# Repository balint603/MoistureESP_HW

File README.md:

# Hardware for MoistureESP project.
## Description
This project aims to use the ESP32 in low power modes, discover its capabilites for low power application. Also, this sensor project would be useful for home gardens not to forget watering.
This is not a complete product, it can be considered as a devboard.

*Software component not published yet.*
*3D case not published yet.*
## Software
See repository: [https://github.com/balint603/moist](https://github.com/balint603/moist)
## Components
- *This PCB project*
- ESP32-WROOM-32
- SOILCAP-V20 humidity measure
- DS18B20 sensor
- *SW not ready yet*
- *BMS configuration not ready yet*
## Features
- BMS cell protection.
- Overvoltage protection for battery input.
- Charger with USB (not tested).
- Wi-Fi MQTT data transmission.
- Selectable sensor measure interval.
## Interfaces
- Wi-Fi communication aimed to be used for sharing sensor data.
- Analog input for moisture sensor board (SOILCAP-V20).
- 1-Wire interface for DS18B20 temperature sensor.
- BMS I2C lines.
- UART for ESP programming and debug with RTS, DTS secondary programming feature.
- *Optional I2C for display.*
## Power
- Sized for 18650 battery cell, BMS tested with NCR18650B.
- Optinally Li-ion charger can be connected.
- Built-in USB charger was not tested.
### BMS configuration
1. Disable 2 cell: Settings->DA configuration->CC0 bit needs to be set to zero.
    - Otherwise it causes CUV and discharge FET will not turn on.
## Prerequisites
- KiCAD v10.0.0 

## Release
- V1.0: USB charger not tested.

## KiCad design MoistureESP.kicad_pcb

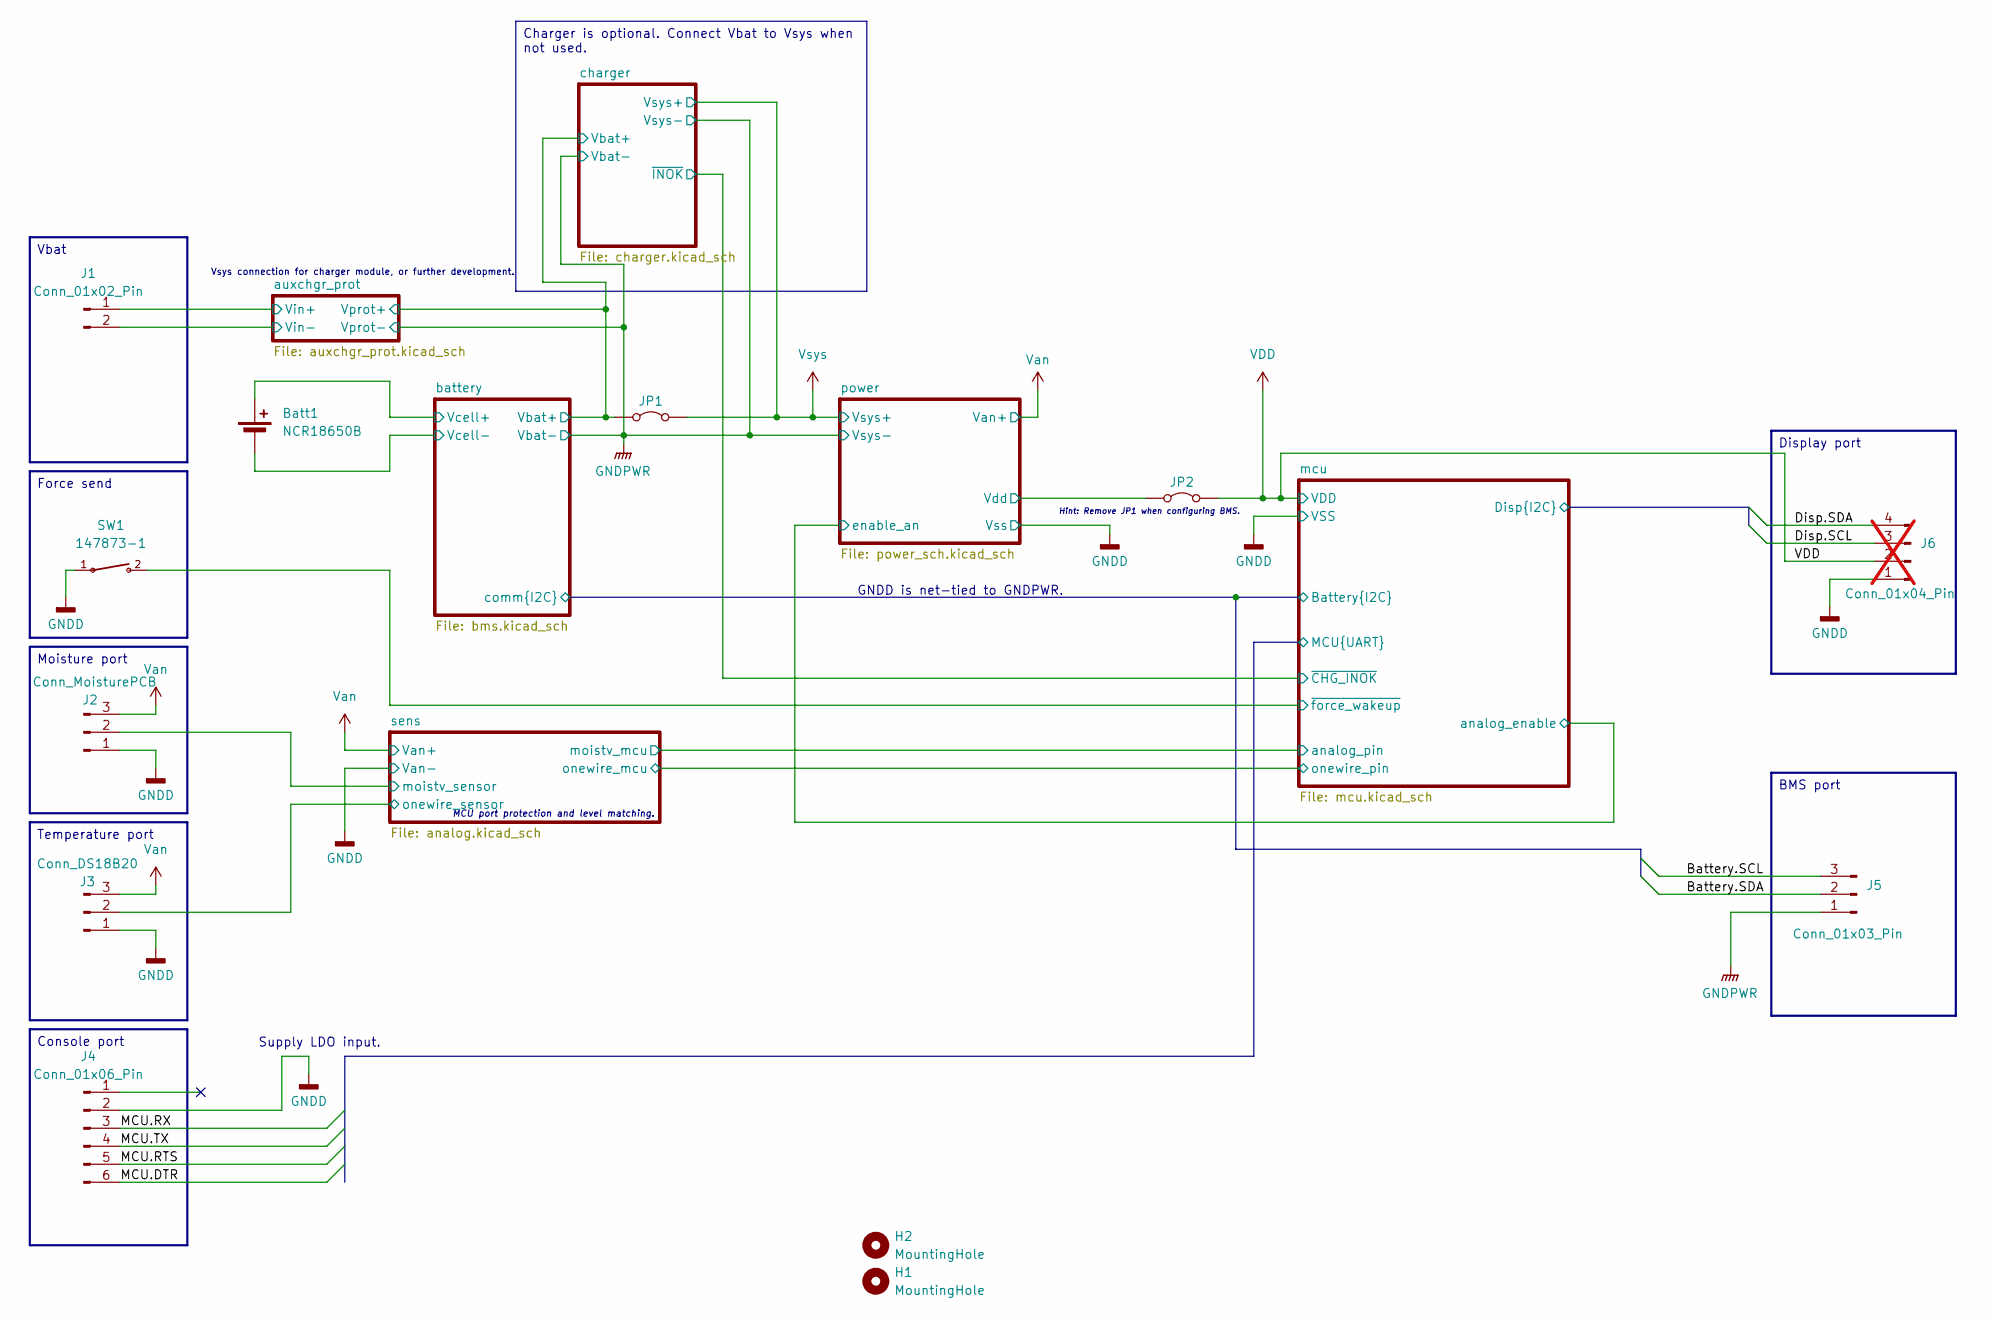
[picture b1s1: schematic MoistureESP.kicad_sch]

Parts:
Batt1: NCR18650B; NCR18650
H1, H2: MountingHole; MountingHole_2.7mm_M2.5_DIN965
J1: Conn_01x02_Pin; PinHeader_1x02_P2.54mm_Vertical
J2: Conn_MoisturePCB; sensorwirepads3x1
J3: Conn_DS18B20; sensorwirepads3x1
J4: Conn_01x06_Pin; PinHeader_1x06_P2.54mm_Vertical
J5: Conn_01x03_Pin; PinHeader_1x03_P2.54mm_Vertical
J6: Conn_01x04_Pin; PinHeader_1x04_P2.54mm_Vertical; not fitted
JP1, JP2: Jumper_2_Bridged; PinHeader_1x02_P2.54mm_Vertical
SW1: 147873-1; SW_147873-1; PARTREV K3

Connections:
/auxchgr_prot/Vin+: J1.1; also elsewhere on the board
/battery/Vcell+: Batt1.1 (+); also elsewhere on the board
/battery/comm.SCL: J5.3; also elsewhere on the board
/battery/comm.SDA: J5.2; also elsewhere on the board
/charger/VBat: JP1.1 (A); also elsewhere on the board
/mcu/Disp.SCL: J6.3; also elsewhere on the board
/mcu/Disp.SDA: J6.4; also elsewhere on the board
/mcu/MCU.DTR: J4.6; also elsewhere on the board
/mcu/MCU.RTS: J4.5; also elsewhere on the board
/mcu/MCU.RX: J4.3; also elsewhere on the board
/mcu/MCU.TX: J4.4; also elsewhere on the board
/mcu/onewire_pin: J3.2; also elsewhere on the board
/mcu/~force_wakeup: SW1.2; also elsewhere on the board
/power/Vdd: JP2.1 (A); also elsewhere on the board
/sens/moistv_sensor: J2.2; also elsewhere on the board
CGND: Batt1.2 (-); also elsewhere on the board
GNDD: J2.1, J3.1, J4.2, J6.1, SW1.1; also elsewhere on the board
GNDPWR: J1.2, J5.1; also elsewhere on the board
VDD: J6.2, JP2.2 (B); also elsewhere on the board
Van: J2.3, J3.3; also elsewhere on the board
Vsys: JP1.2 (B); also elsewhere on the board

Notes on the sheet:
Vsys connection for charger module, or further development.
MCU port protection and level matching.
Supply LDO input.
GNDD is net-tied to GNDPWR.
Hint: Remove JP1 when configuring BMS.
Vbat
Temperature port
Force send
Console port
Charger is optional. Connect Vbat to Vsys when not used.
Display port
BMS port
Moisture port

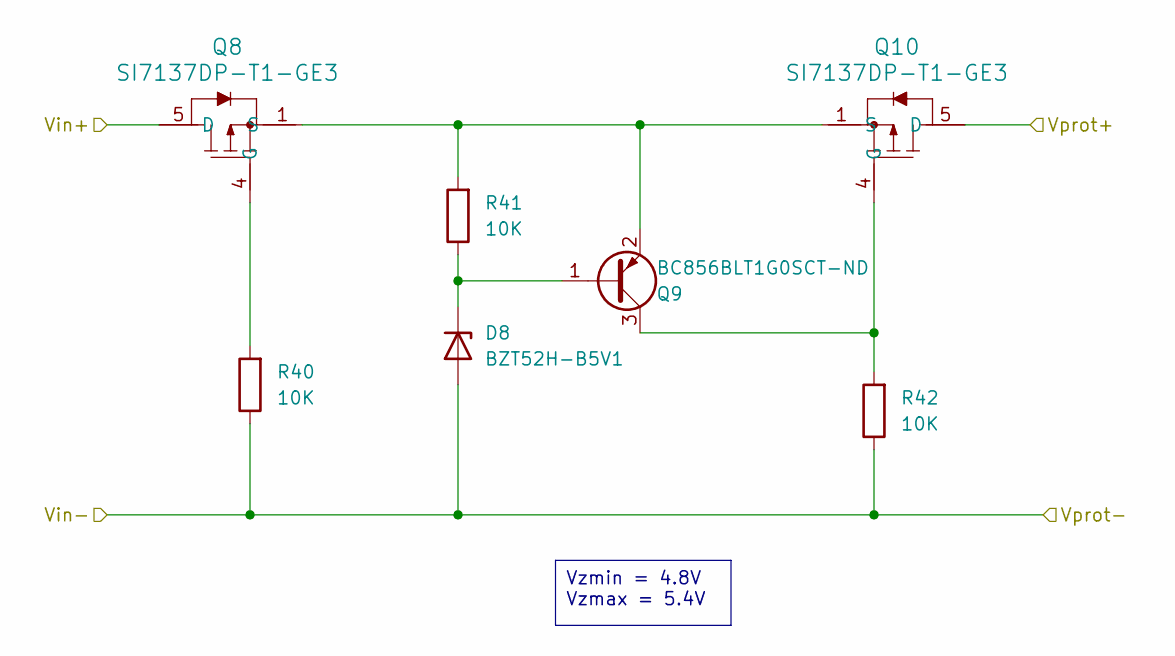
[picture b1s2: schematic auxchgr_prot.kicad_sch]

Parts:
D8: BZT52H-B5V1; D_SOD-123F
Q8, Q10: SI7137DP-T1-GE3; MOSFET_7DP-T1-GE3_VIS
Q9: BC856BLT1G0SCT-ND; SOT-23
R40, R41, R42: 10K; R_0603_1608Metric_Pad0.98x0.95mm_HandSolder

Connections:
/auxchgr_prot/Vin+: Q8.5 (D); also elsewhere on the board
/charger/VBat: Q10.5 (D); also elsewhere on the board
GNDPWR: D8.2 (A), R40.1, R42.1; also elsewhere on the board
unnamed: D8.1 (K), Q9.1 (B), R41.1
unnamed: Q8.4 (G), R40.2
unnamed: Q8.1 (S), Q8.2 (S), Q8.3 (S), Q9.2 (E), Q10.1 (S), Q10.2 (S), Q10.3 (S), R41.2
unnamed: Q9.3 (C), Q10.4 (G), R42.2

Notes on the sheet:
Vzmin = 4.8V Vzmax = 5.4V

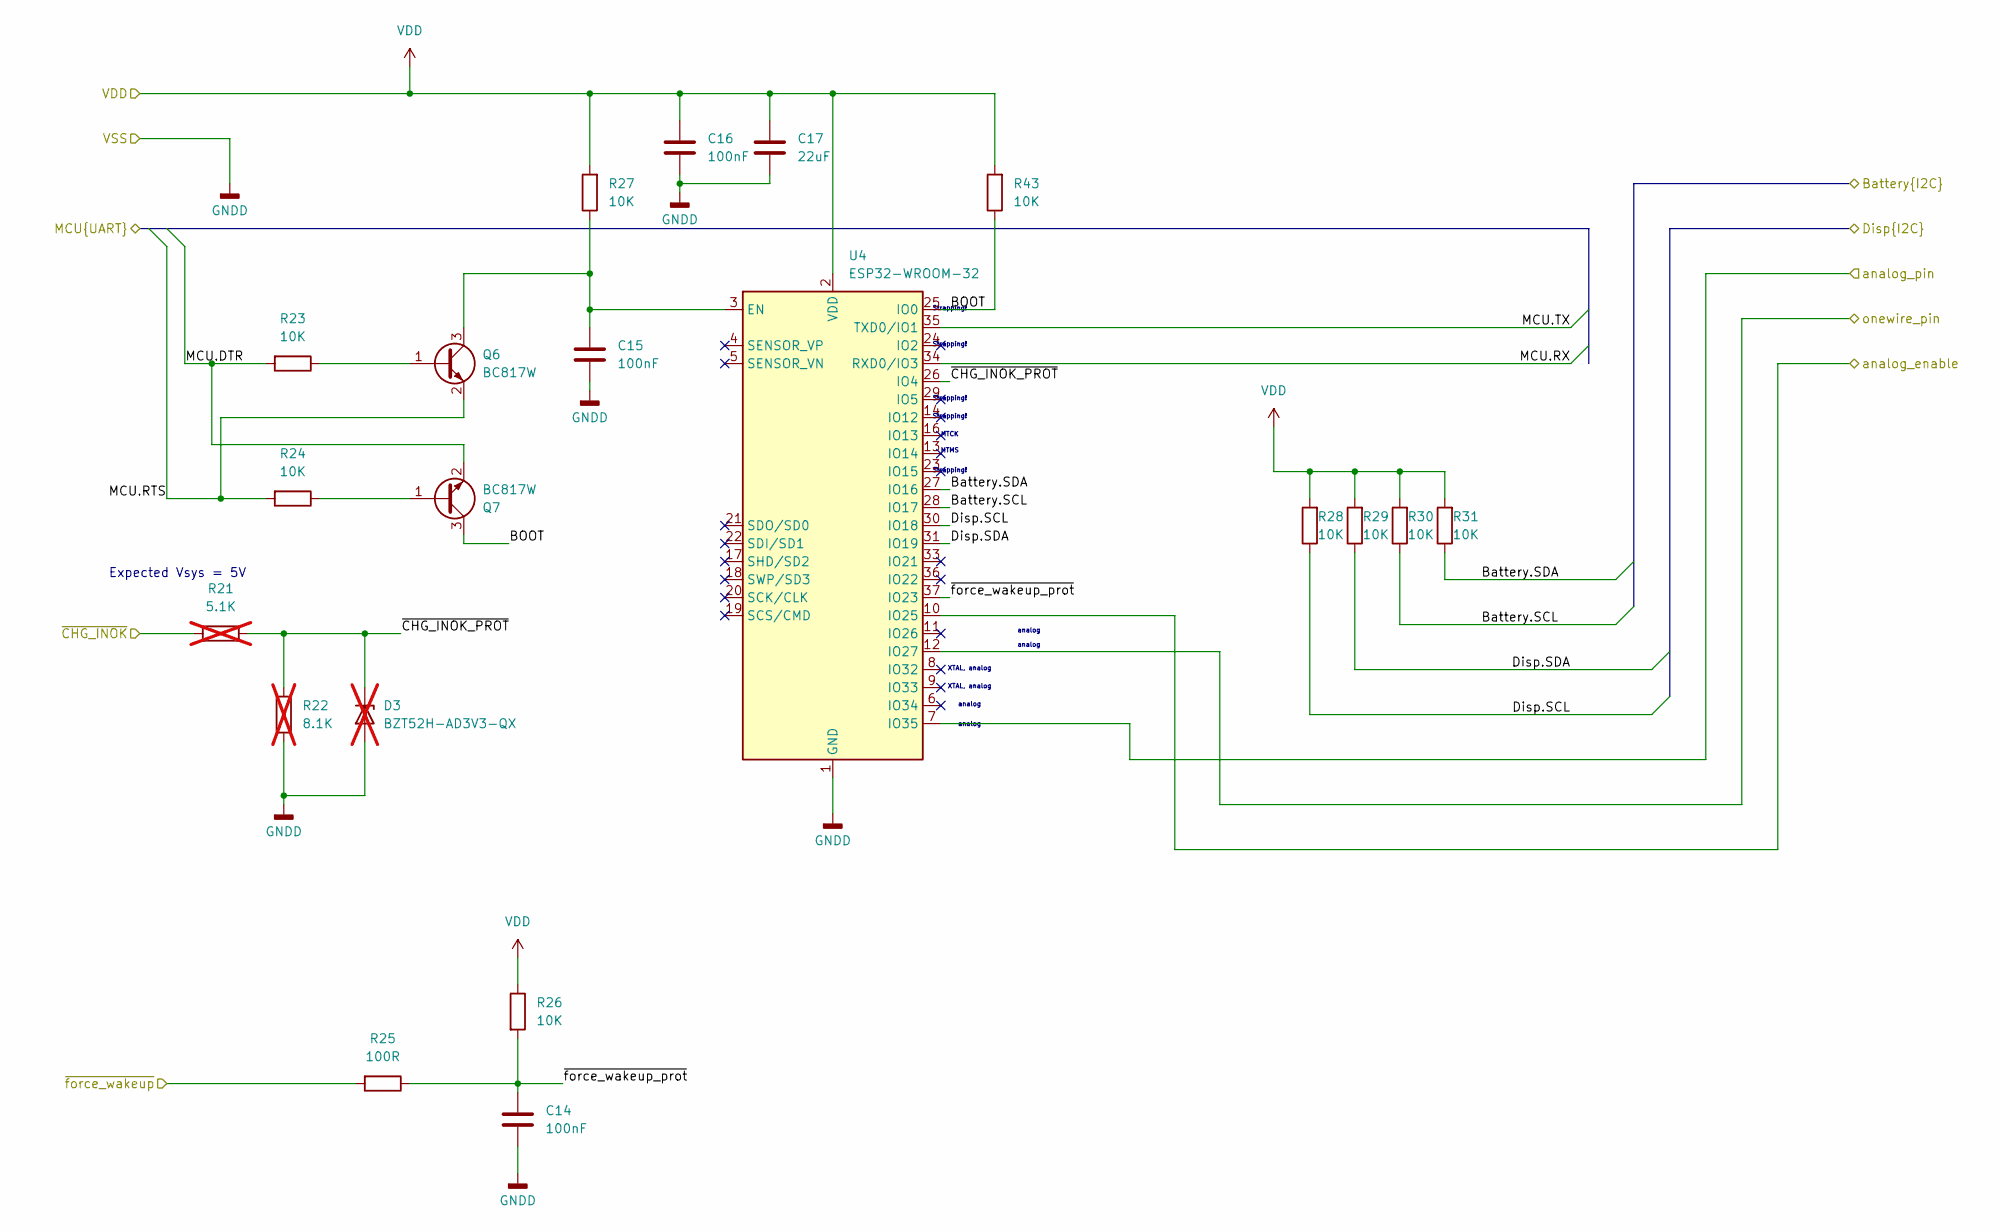
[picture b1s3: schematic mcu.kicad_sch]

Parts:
C14, C15, C16: 100nF; C_0603_1608Metric_Pad1.08x0.95mm_HandSolder; Voltage 25V
C17: 22uF; C_0603_1608Metric_Pad1.08x0.95mm_HandSolder; Voltage 10V
D3: BZT52H-AD3V3-QX; D_SOD-123F; not fitted
Q6, Q7: BC817W; SOT-323_SC-70
R21: 5.1K; R_0603_1608Metric_Pad0.98x0.95mm_HandSolder; not fitted
R22: 8.1K; R_0603_1608Metric_Pad0.98x0.95mm_HandSolder; not fitted
R23, R24, R26, R27, R28, R29, R30, R31, R43: 10K; R_0603_1608Metric_Pad0.98x0.95mm_HandSolder
R25: 100R; R_0603_1608Metric_Pad0.98x0.95mm_HandSolder
U4: ESP32-WROOM-32

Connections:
/battery/comm.SCL: R30.1, U4.28 (IO17); also elsewhere on the board
/battery/comm.SDA: R31.1, U4.27 (IO16); also elsewhere on the board
/charger/~INOK: R21.2; also elsewhere on the board
/mcu/BOOT: Q7.3 (C), R43.1, U4.25 (IO0)
/mcu/Disp.SCL: R28.1, U4.30 (IO18); also elsewhere on the board
/mcu/Disp.SDA: R29.1, U4.31 (IO19); also elsewhere on the board
/mcu/MCU.DTR: Q7.2 (E), R23.2; also elsewhere on the board
/mcu/MCU.RTS: Q6.2 (E), R24.2; also elsewhere on the board
/mcu/MCU.RX: U4.34 (RXD0/IO3); also elsewhere on the board
/mcu/MCU.TX: U4.35 (TXD0/IO1); also elsewhere on the board
/mcu/analog_enable: U4.10 (IO25); also elsewhere on the board
/mcu/analog_pin: U4.7 (IO35); also elsewhere on the board
/mcu/onewire_pin: U4.12 (IO27); also elsewhere on the board
/mcu/~CHG_INOK_PROT: D3.1 (K), R21.1, R22.1, U4.26 (IO4)
/mcu/~force_wakeup_prot: C14.1, R25.1, R26.2, U4.37 (IO23)
/mcu/~force_wakeup: R25.2; also elsewhere on the board
GNDD: C14.2, C15.2, C16.2, C17.2, D3.2 (A), R22.2, U4.1 (GND), U4.15 (GND), U4.38 (GND), U4.39 (GND); also elsewhere on the board
unnamed: Q6.1 (B), R23.1
unnamed: C15.1, Q6.3 (C), R27.1, U4.3 (EN)
unnamed: Q7.1 (B), R24.1
VDD: C16.1, C17.1, R26.1, R27.2, R28.2, R29.2, R30.2, R31.2, R43.2, U4.2 (VDD); also elsewhere on the board

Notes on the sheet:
analog
XTAL, analog
Strapping!
MTCK
Expected Vsys = 5V
MTMS

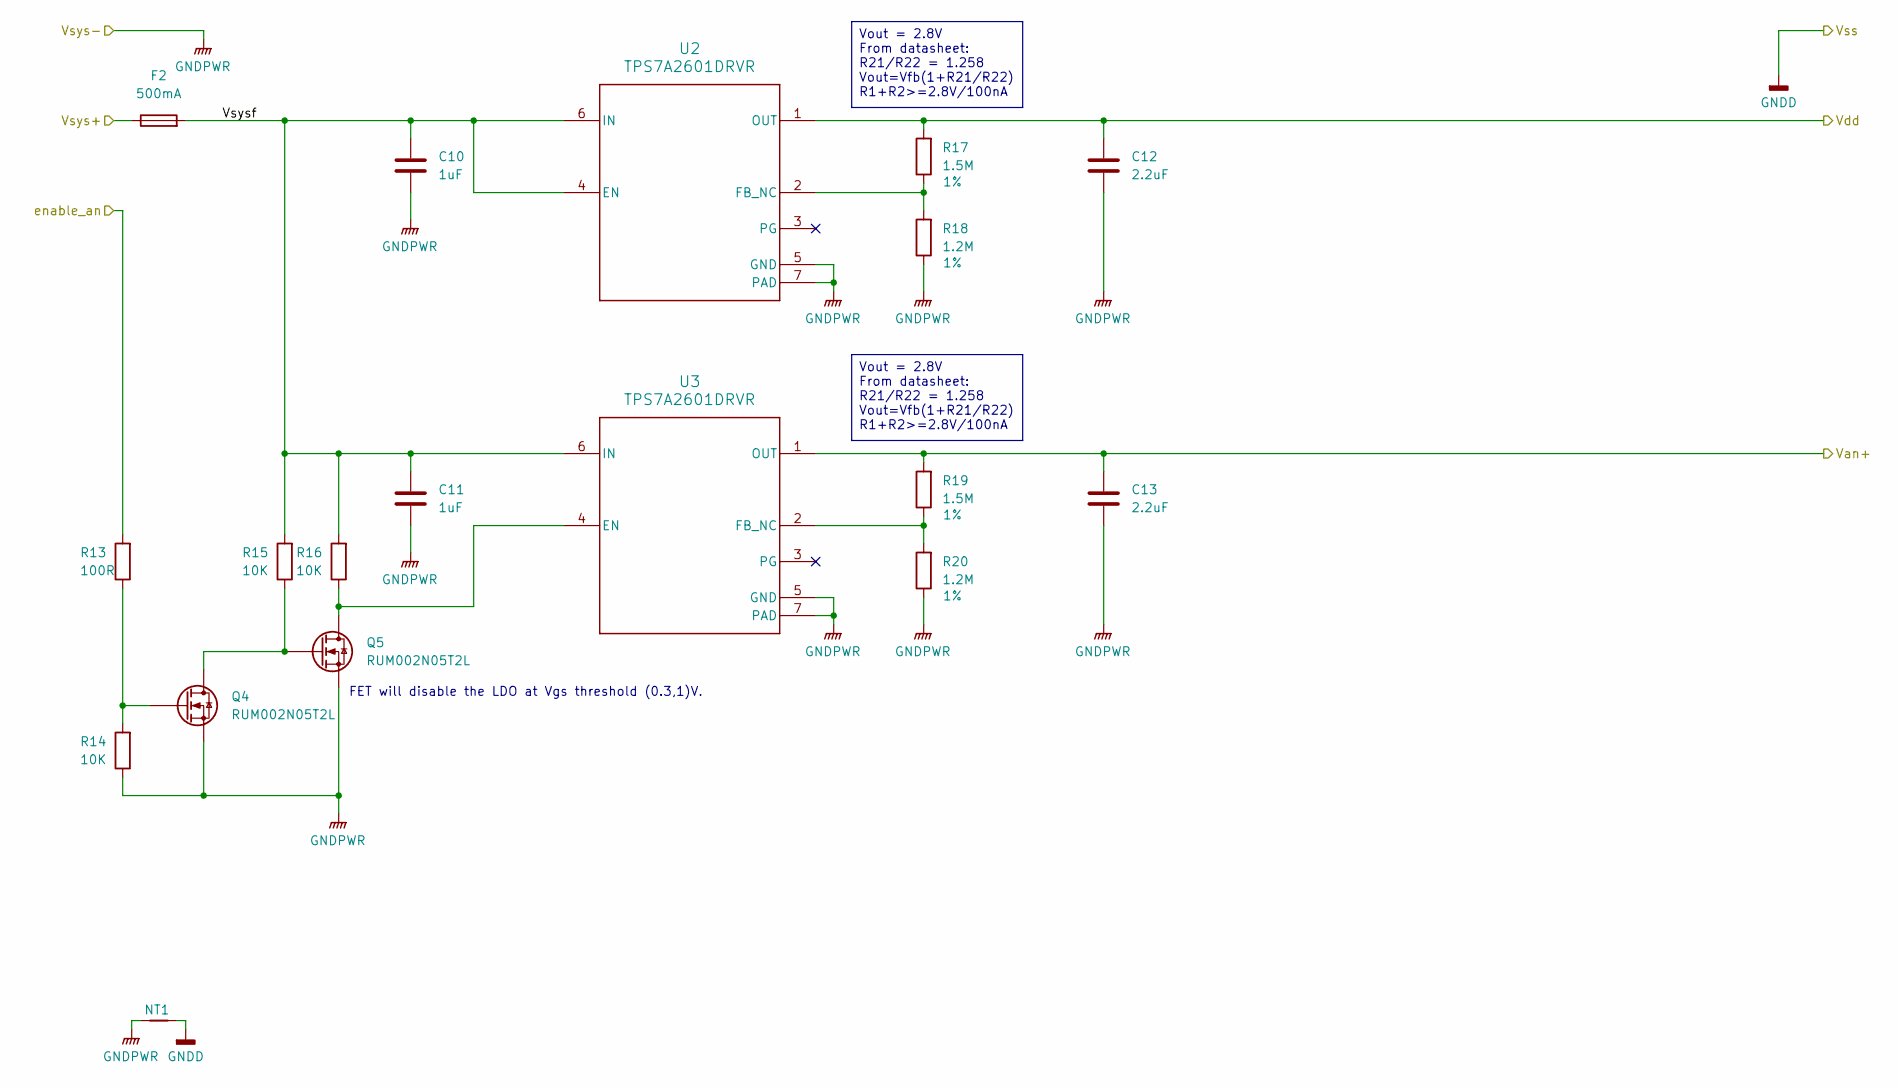
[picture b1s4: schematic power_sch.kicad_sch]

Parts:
C10, C11: 1uF; C_0603_1608Metric_Pad1.08x0.95mm_HandSolder
C12, C13: 2.2uF; C_0603_1608Metric_Pad1.08x0.95mm_HandSolder
F2: 500mA; R_1206_3216Metric_Pad1.30x1.75mm_HandSolder
NT1: NetTie_2; NetTie-2_SMD_Pad2.0mm
Q4, Q5: RUM002N05T2L; SOT-723
R13: 100R; R_0603_1608Metric_Pad0.98x0.95mm_HandSolder
R14, R15, R16: 10K; R_0603_1608Metric_Pad0.98x0.95mm_HandSolder
R17, R19: 1.5M; R_0603_1608Metric_Pad0.98x0.95mm_HandSolder; Tolerance 1%
R18, R20: 1.2M; R_0603_1608Metric_Pad0.98x0.95mm_HandSolder; Tolerance 1%
U2, U3: TPS7A2601DRVR; DRV0006A

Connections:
/mcu/analog_enable: R13.2; also elsewhere on the board
/power/Vdd: C12.2, R17.2, U2.1 (OUT); also elsewhere on the board
/power/Vsysf: C10.2, C11.2, F2.2, R15.2, R16.2, U2.4 (EN), U2.6 (IN), U3.6 (IN)
GNDD: NT1.2; also elsewhere on the board
GNDPWR: C10.1, C11.1, C12.1, C13.1, NT1.1, Q4.2 (S), Q5.2 (S), R14.1, R18.1, R20.1, U2.5 (GND), U2.7 (PAD), U3.5 (GND), U3.7 (PAD); also elsewhere on the board
unnamed: Q4.3 (D), Q5.1 (G), R15.1
unnamed: Q4.1 (G), R13.1, R14.2
unnamed: Q5.3 (D), R16.1, U3.4 (EN)
unnamed: R17.1, R18.2, U2.2 (FB_NC)
unnamed: R19.1, R20.2, U3.2 (FB_NC)
Van: C13.2, R19.2, U3.1 (OUT); also elsewhere on the board
Vsys: F2.1; also elsewhere on the board

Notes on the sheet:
FET will disable the LDO at Vgs threshold (0.3,1)V.
Vout = 2.8V From datasheet: R21/R22 = 1.258 Vout=Vfb(1+R21/R22) R1+R2>=2.8V/100nA

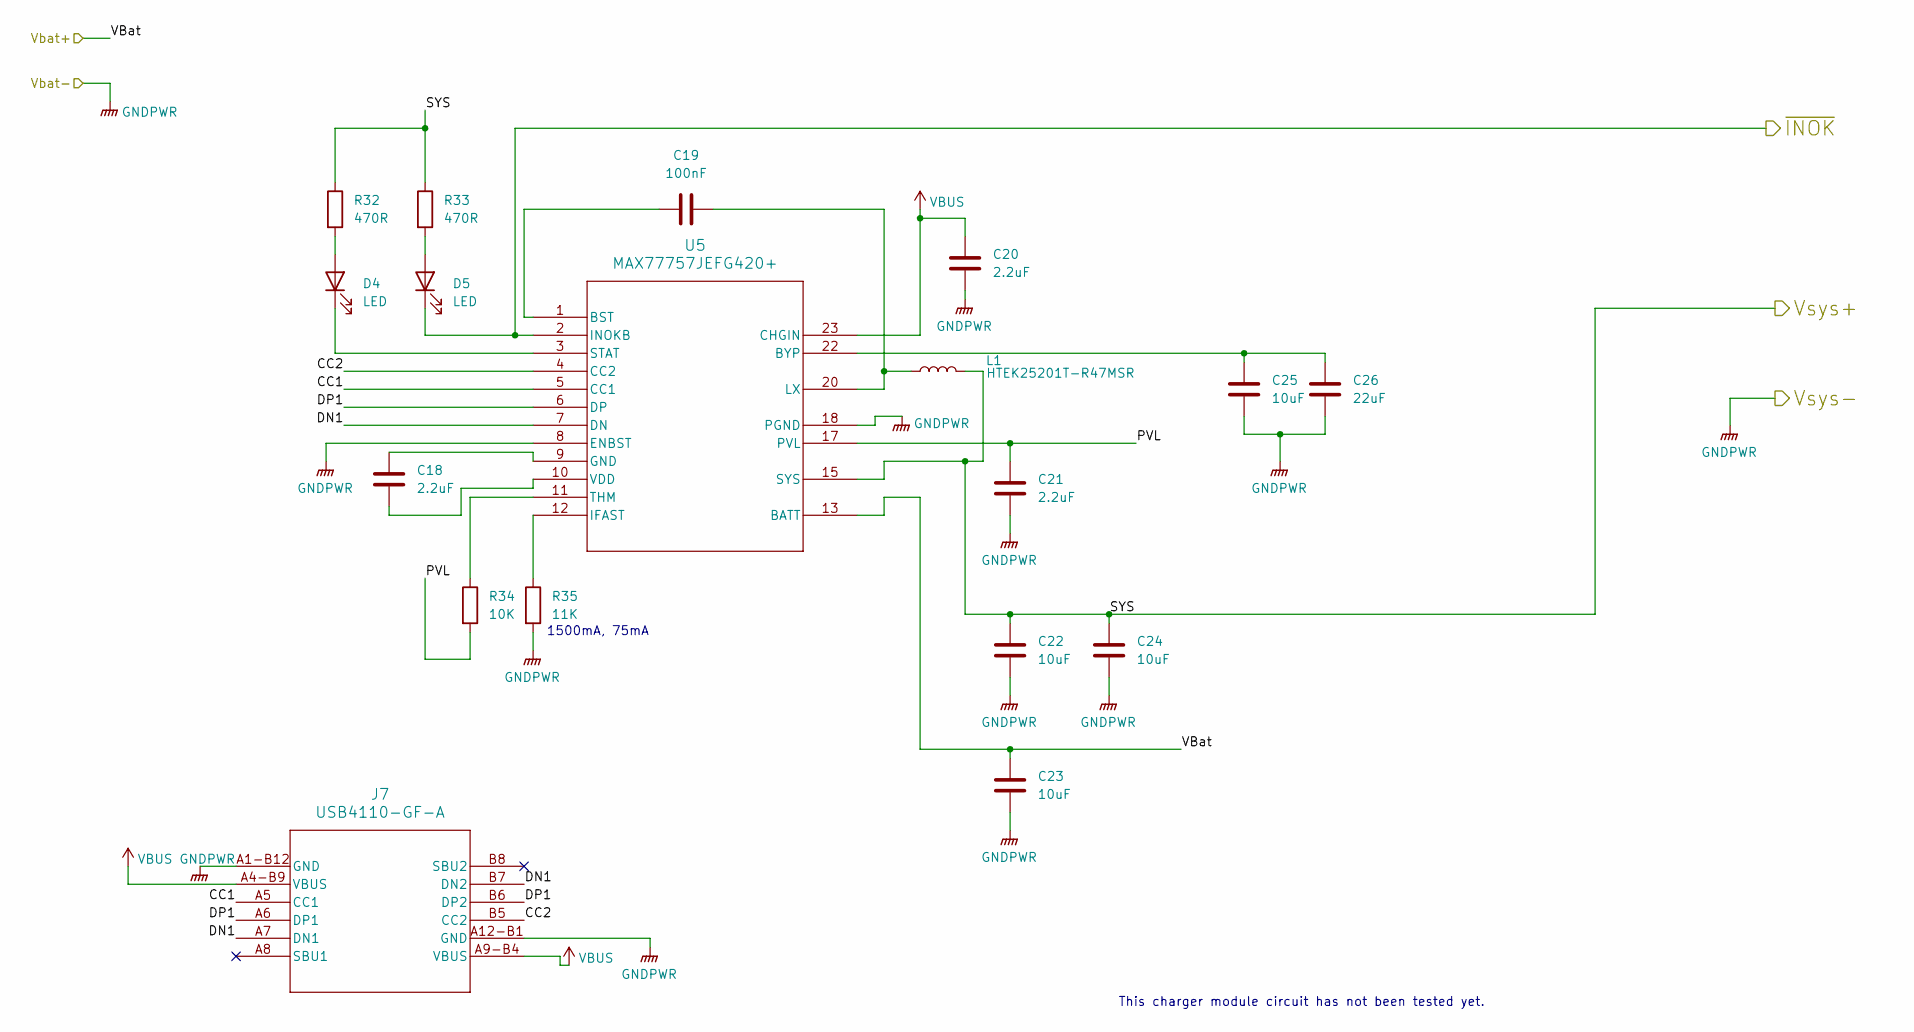
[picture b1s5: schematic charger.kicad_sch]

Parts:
C18, C20, C21: 2.2uF; C_0603_1608Metric_Pad1.08x0.95mm_HandSolder; Voltage 25V
C19: 100nF; C_0603_1608Metric_Pad1.08x0.95mm_HandSolder; Voltage 25V
C22, C23, C24, C25: 10uF; C_0603_1608Metric_Pad1.08x0.95mm_HandSolder; Voltage 25V
C26: 22uF; C_0603_1608Metric_Pad1.08x0.95mm_HandSolder; Voltage 25V
D4, D5: LED; LED_0603_1608Metric
J7: USB4110-GF-A; USB4110-GF-A_GCT
L1: HTEK25201T-R47MSR; L_1008_2520Metric_Pad1.43x2.20mm_HandSolder
R32, R33: 470R; R_0603_1608Metric_Pad0.98x0.95mm_HandSolder
R34: 10K; R_0603_1608Metric_Pad0.98x0.95mm_HandSolder
R35: 11K; R_0603_1608Metric_Pad0.98x0.95mm_HandSolder
U5: MAX77757JEFG420+; 21-100385B_90-100128_MXM

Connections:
/charger/CC1: J7.A5 (CC1), U5.5 (CC1)
/charger/CC2: J7.B5 (CC2), U5.4 (CC2)
/charger/DN1: J7.A7 (DN1), J7.B7 (DN2), U5.7 (DN)
/charger/DP1: J7.A6 (DP1), J7.B6 (DP2), U5.6 (DP)
/charger/PVL: C21.2, R34.2, U5.17 (PVL)
/charger/VBat: C23.2, U5.13 (BATT); also elsewhere on the board
/charger/~INOK: D5.1 (K), U5.2 (INOKB); also elsewhere on the board
GNDPWR: C20.1, C21.1, C22.1, C23.1, C24.1, C25.1, C26.1, J7.A1-B12 (GND), J7.A12-B1 (GND), R35.2, U5.8 (ENBST), U5.18 (PGND); also elsewhere on the board
unnamed: D4.2 (A), R32.2
unnamed: D4.1 (K), U5.3 (STAT)
unnamed: D5.2 (A), R33.2
unnamed: C19.2, U5.1 (BST)
unnamed: C25.2, C26.2, U5.22 (BYP)
unnamed: C18.2, U5.9 (GND)
unnamed: R35.1, U5.12 (IFAST)
unnamed: C19.1, L1.1, U5.20 (LX)
unnamed: R34.1, U5.11 (THM)
unnamed: C18.1, U5.10 (VDD)
VBUS: C20.2, J7.A4-B9 (VBUS), J7.A9-B4 (VBUS), U5.23 (CHGIN)
Vsys: C22.2, C24.2, L1.2, R32.1, R33.1, U5.15 (SYS); also elsewhere on the board

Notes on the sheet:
1500mA, 75mA
This charger module circuit has not been tested yet.

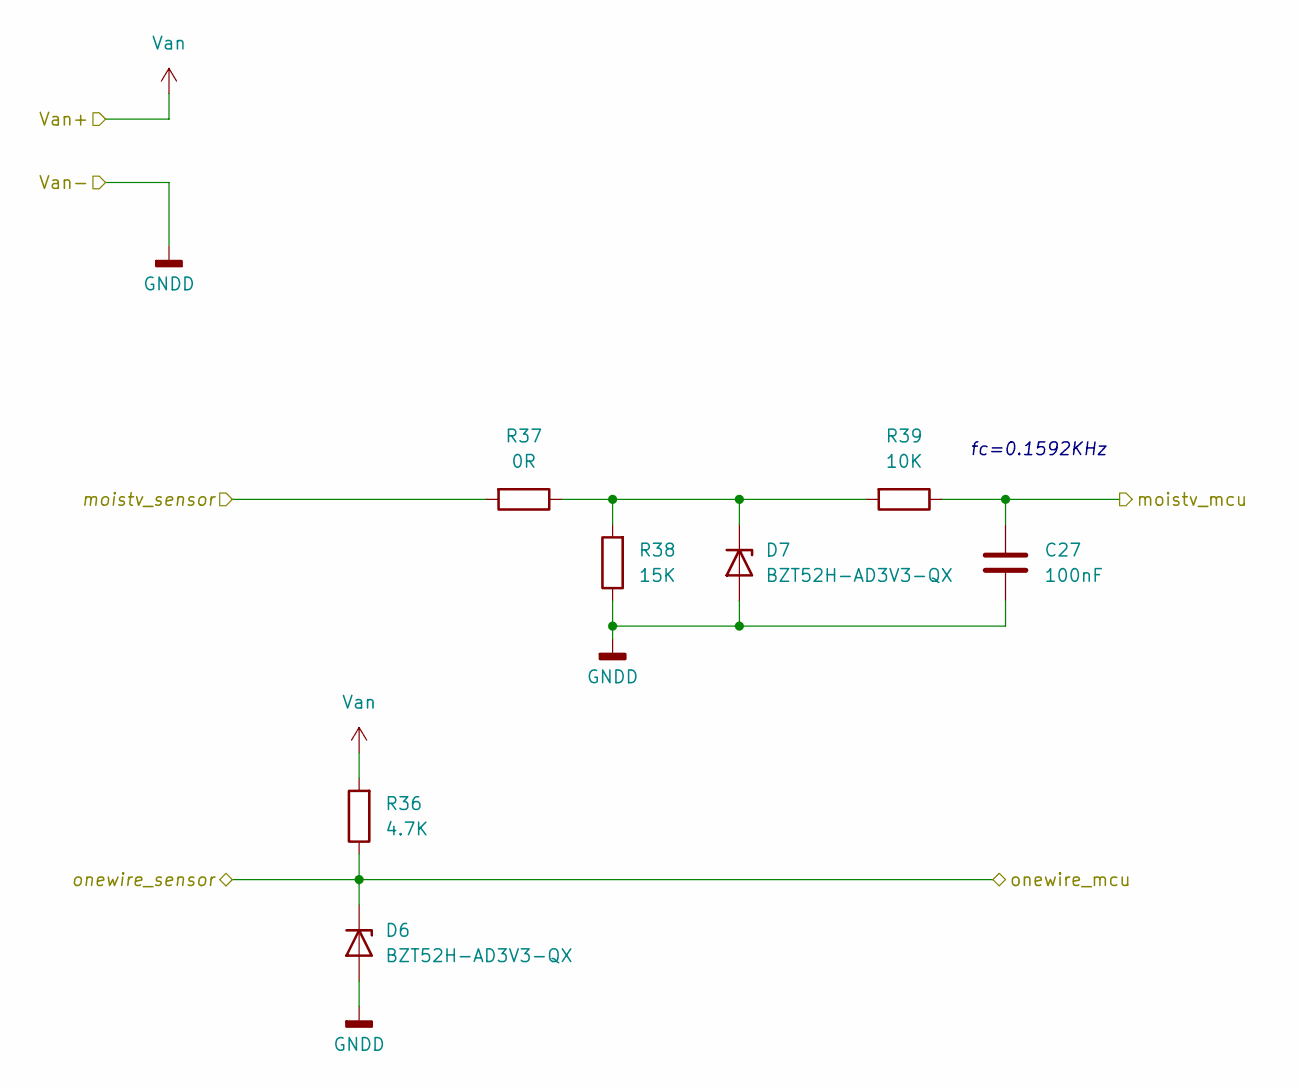
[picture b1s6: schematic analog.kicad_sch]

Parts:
C27: 100nF; C_0603_1608Metric_Pad1.08x0.95mm_HandSolder
D6, D7: BZT52H-AD3V3-QX; D_SOD-123F
R36: 4.7K; R_0603_1608Metric_Pad0.98x0.95mm_HandSolder
R37: 0R; R_0603_1608Metric_Pad0.98x0.95mm_HandSolder
R38: 15K; R_0603_1608Metric_Pad0.98x0.95mm_HandSolder
R39: 10K; R_0603_1608Metric_Pad0.98x0.95mm_HandSolder

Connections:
/mcu/analog_pin: C27.2, R39.1; also elsewhere on the board
/mcu/onewire_pin: D6.1 (K), R36.1; also elsewhere on the board
/sens/moistv_sensor: R37.2; also elsewhere on the board
GNDD: C27.1, D6.2 (A), D7.2 (A), R38.1; also elsewhere on the board
unnamed: D7.1 (K), R37.1, R38.2, R39.2
Van: R36.2; also elsewhere on the board

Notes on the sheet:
fc=0.1592KHz

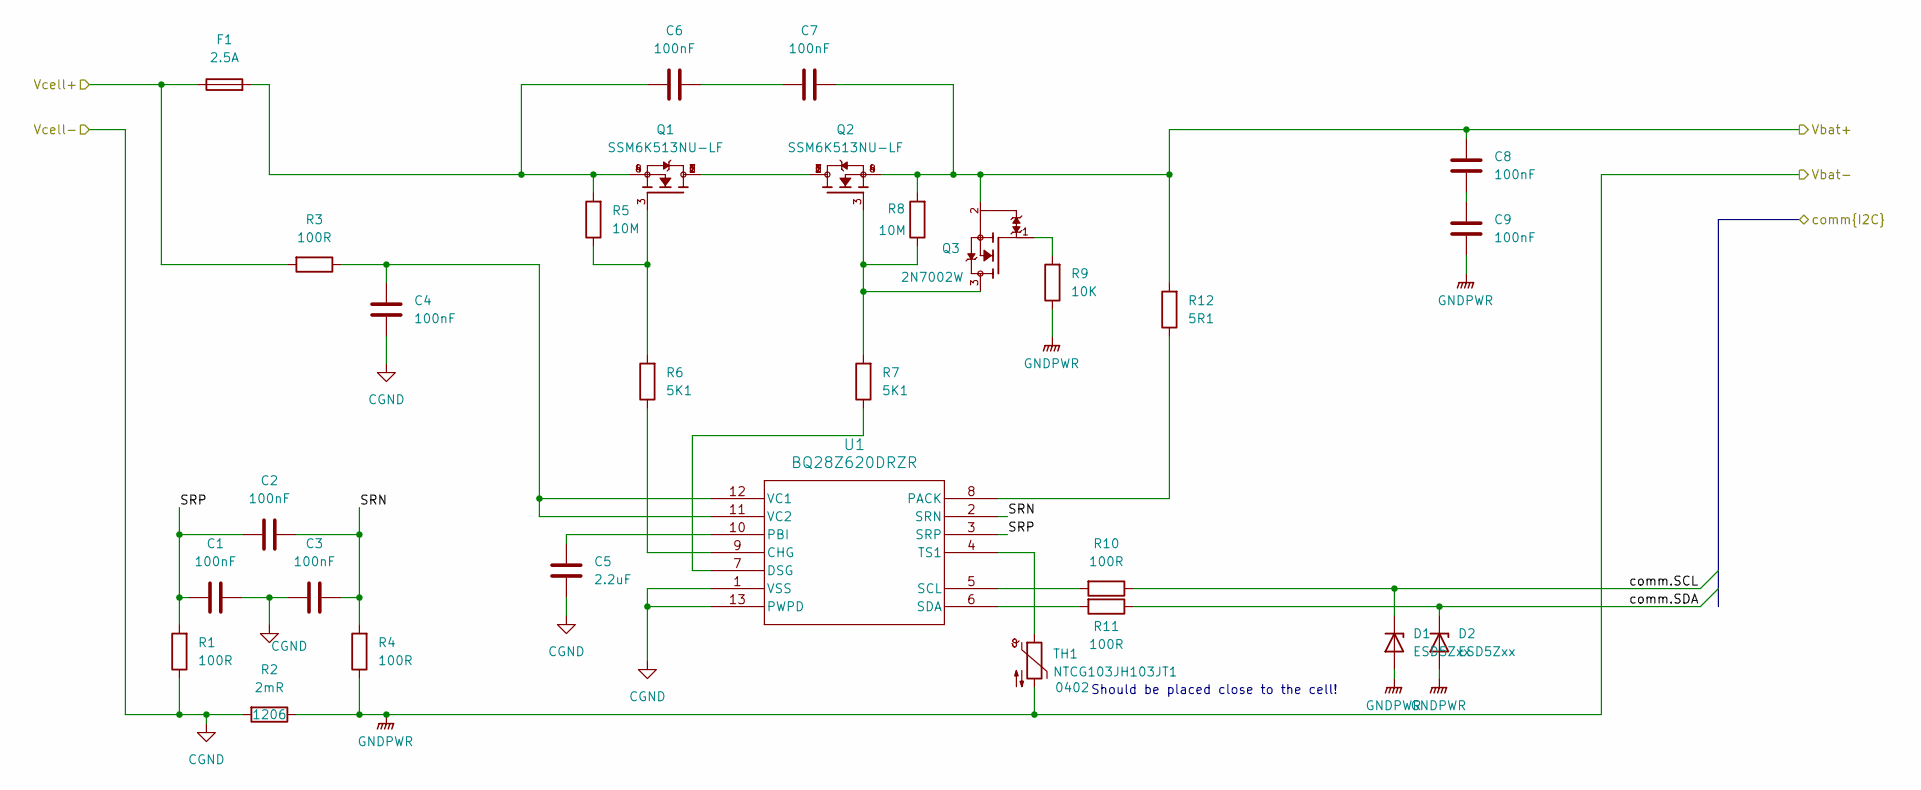
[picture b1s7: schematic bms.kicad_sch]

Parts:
C1, C2, C3, C4, C6, C7, C8, C9: 100nF; C_0603_1608Metric_Pad1.08x0.95mm_HandSolder
C5: 2.2uF; C_0603_1608Metric_Pad1.08x0.95mm_HandSolder
D1, D2: ESD5Zxx; D_SOD-523
F1: 2.5A; R_0603_1608Metric_Pad0.98x0.95mm_HandSolder
Q1, Q2: SSM6K513NU-LF; TRANS_SSM6K513NU-LF
Q3: 2N7002W; SOT65P220X100-3N
R1, R3, R4, R10, R11: 100R; R_0603_1608Metric_Pad0.98x0.95mm_HandSolder
R2: 2mR; R_1206_3216Metric_Pad1.30x1.75mm_HandSolder; Tolerance 1%
R5, R8: 10M; R_0603_1608Metric_Pad0.98x0.95mm_HandSolder
R6, R7: 5K1; R_0603_1608Metric_Pad0.98x0.95mm_HandSolder
R9: 10K; R_0603_1608Metric_Pad0.98x0.95mm_HandSolder
R12: 5R1; R_0603_1608Metric_Pad0.98x0.95mm_HandSolder
TH1: NTCG103JH103JT1; R_0402_1005Metric_Pad0.72x0.64mm_HandSolder
U1: BQ28Z620DRZR; VSON12_DRZ_TEX-L

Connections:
/battery/SRN: C2.2, C3.2, R4.2, U1.2 (SRN)
/battery/SRP: C1.1, C2.1, R1.2, U1.3 (SRP)
/battery/Vcell+: F1.1, R3.2; also elsewhere on the board
/battery/comm.SCL: D1.1 (K), R10.1; also elsewhere on the board
/battery/comm.SDA: D2.1 (K), R11.1; also elsewhere on the board
/charger/VBat: C7.2, C8.2, Q2.4, Q2.8, Q3.2, R8.2, R12.2; also elsewhere on the board
CGND: C1.2, C3.1, C4.1, C5.1, R1.1, R2.2, U1.1 (VSS), U1.13 (PWPD); also elsewhere on the board
GNDPWR: C9.1, D1.2 (A), D2.2 (A), R2.1, R4.1, R9.1, TH1.2; also elsewhere on the board
unnamed: C6.1, F1.2, Q1.4, Q1.8, R5.2
unnamed: C6.2, C7.1
unnamed: C8.1, C9.2
unnamed: Q1.1, Q1.2, Q1.5, Q1.6, Q1.7, Q2.1, Q2.2, Q2.5, Q2.6, Q2.7
unnamed: Q1.3, R5.1, R6.2
unnamed: Q2.3, Q3.3, R7.2, R8.1
unnamed: Q3.1, R9.2
unnamed: R6.1, U1.9 (CHG)
unnamed: R7.1, U1.7 (DSG)
unnamed: R12.1, U1.8 (PACK)
unnamed: C5.2, U1.10 (PBI)
unnamed: R10.2, U1.5 (SCL)
unnamed: R11.2, U1.6 (SDA)
unnamed: TH1.1, U1.4 (TS1)
unnamed: C4.2, R3.1, U1.11 (VC2), U1.12 (VC1)

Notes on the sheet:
Should be placed close to the cell!

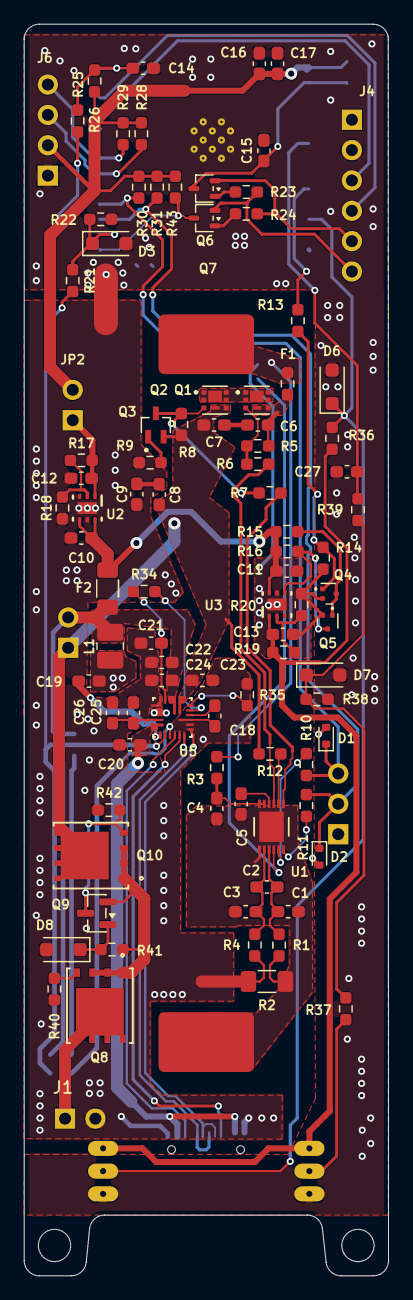
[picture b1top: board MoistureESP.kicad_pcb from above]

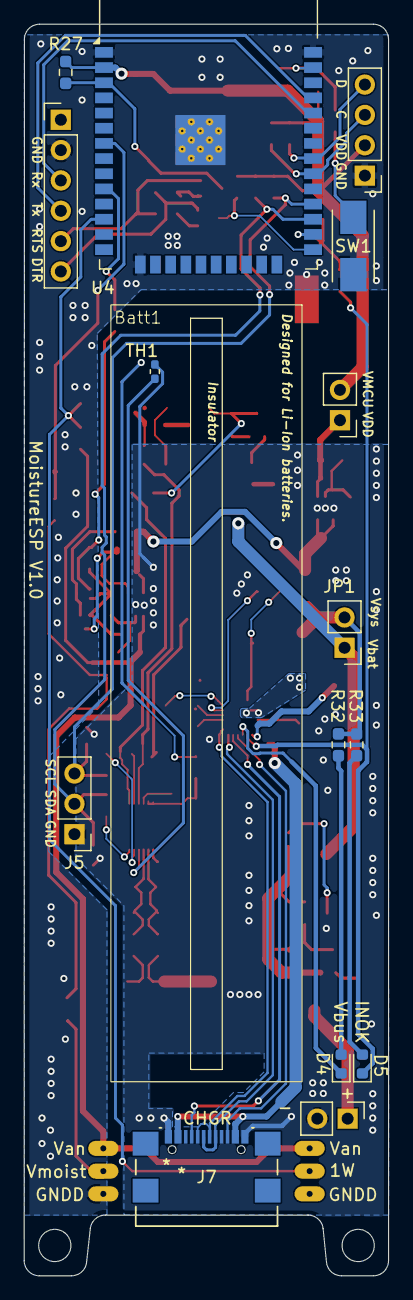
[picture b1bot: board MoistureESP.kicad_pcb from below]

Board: 2 copper layers, 30.5 x 104.8 mm, 111 parts (15 on the bottom side), 74 nets.

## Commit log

2026-03-28 Initial
2026-03-28 Add readme.
2026-03-28 Batter scematic done.
2026-03-28 Draw power schematic.
2026-03-28 Change BJT to FET in MCU. Add pinout.
2026-03-29 Add analog schematic and refine wiring on top.
2026-03-29 Add charger, battery cell.
2026-03-30 Add console port.
2026-03-30 Fix issues
2026-03-30 Fix issues from Issue#1
2026-03-30 Refine wirings.
2026-03-30 Add protected Vbat charger input.
2026-03-30 Fix wrong wiring, add pcb design.
2026-03-30 Add footprint to debug connector.
2026-03-31 Start placement
2026-04-01 Add someplacement.
2026-04-01 Change protection FETs and add resistor.
2026-04-01 Placement concept is finished.
2026-04-02 Add wiring, change footprint to avoid fatal errors at pads.
2026-04-04 Add VBAT polygon, add BQ control wiring.
2026-04-04 Fix BQ cell voltage wrong connection.
2026-04-04 Change USB charger position, redraw the zones.
2026-04-05 Change CGND connection to shunt resistor, change zone hierarchy.
2026-04-06 Refine VBAT zone and add wiring under MCU.
2026-04-07 Layout is finished with adding analog part, wiring the MCU ports and adding GNDD zones. Also add the nettie.
2026-04-07 Fixing DRCs. Modify polygons.
2026-04-08 Fix the actual DRC errors, add 3D model for cell. Fix also BQ28Z610 model.
2026-04-10 Fix ESP32 GPIO wiring, many bootstrap pins were used.
2026-04-13 Editing layout, redrawing analog and RTS DTS signals. Placing the silk layer designators
2026-04-13 Modify zones and adjustmenents in analog power.
2026-04-14 Edit silkscreen.
2026-04-14 Editing silkscreen, move battery charge connector.
2026-04-15 Layout modification, refine connections and zone shapes.
2026-04-15 Finish refinements, prepare to release.
2026-04-15 Add drill files.
2026-04-21 Revised, not found anything.
2026-04-21 Add to README.md
2026-04-24 Export BOM, change page headers.
2026-05-18 Change readme document.
